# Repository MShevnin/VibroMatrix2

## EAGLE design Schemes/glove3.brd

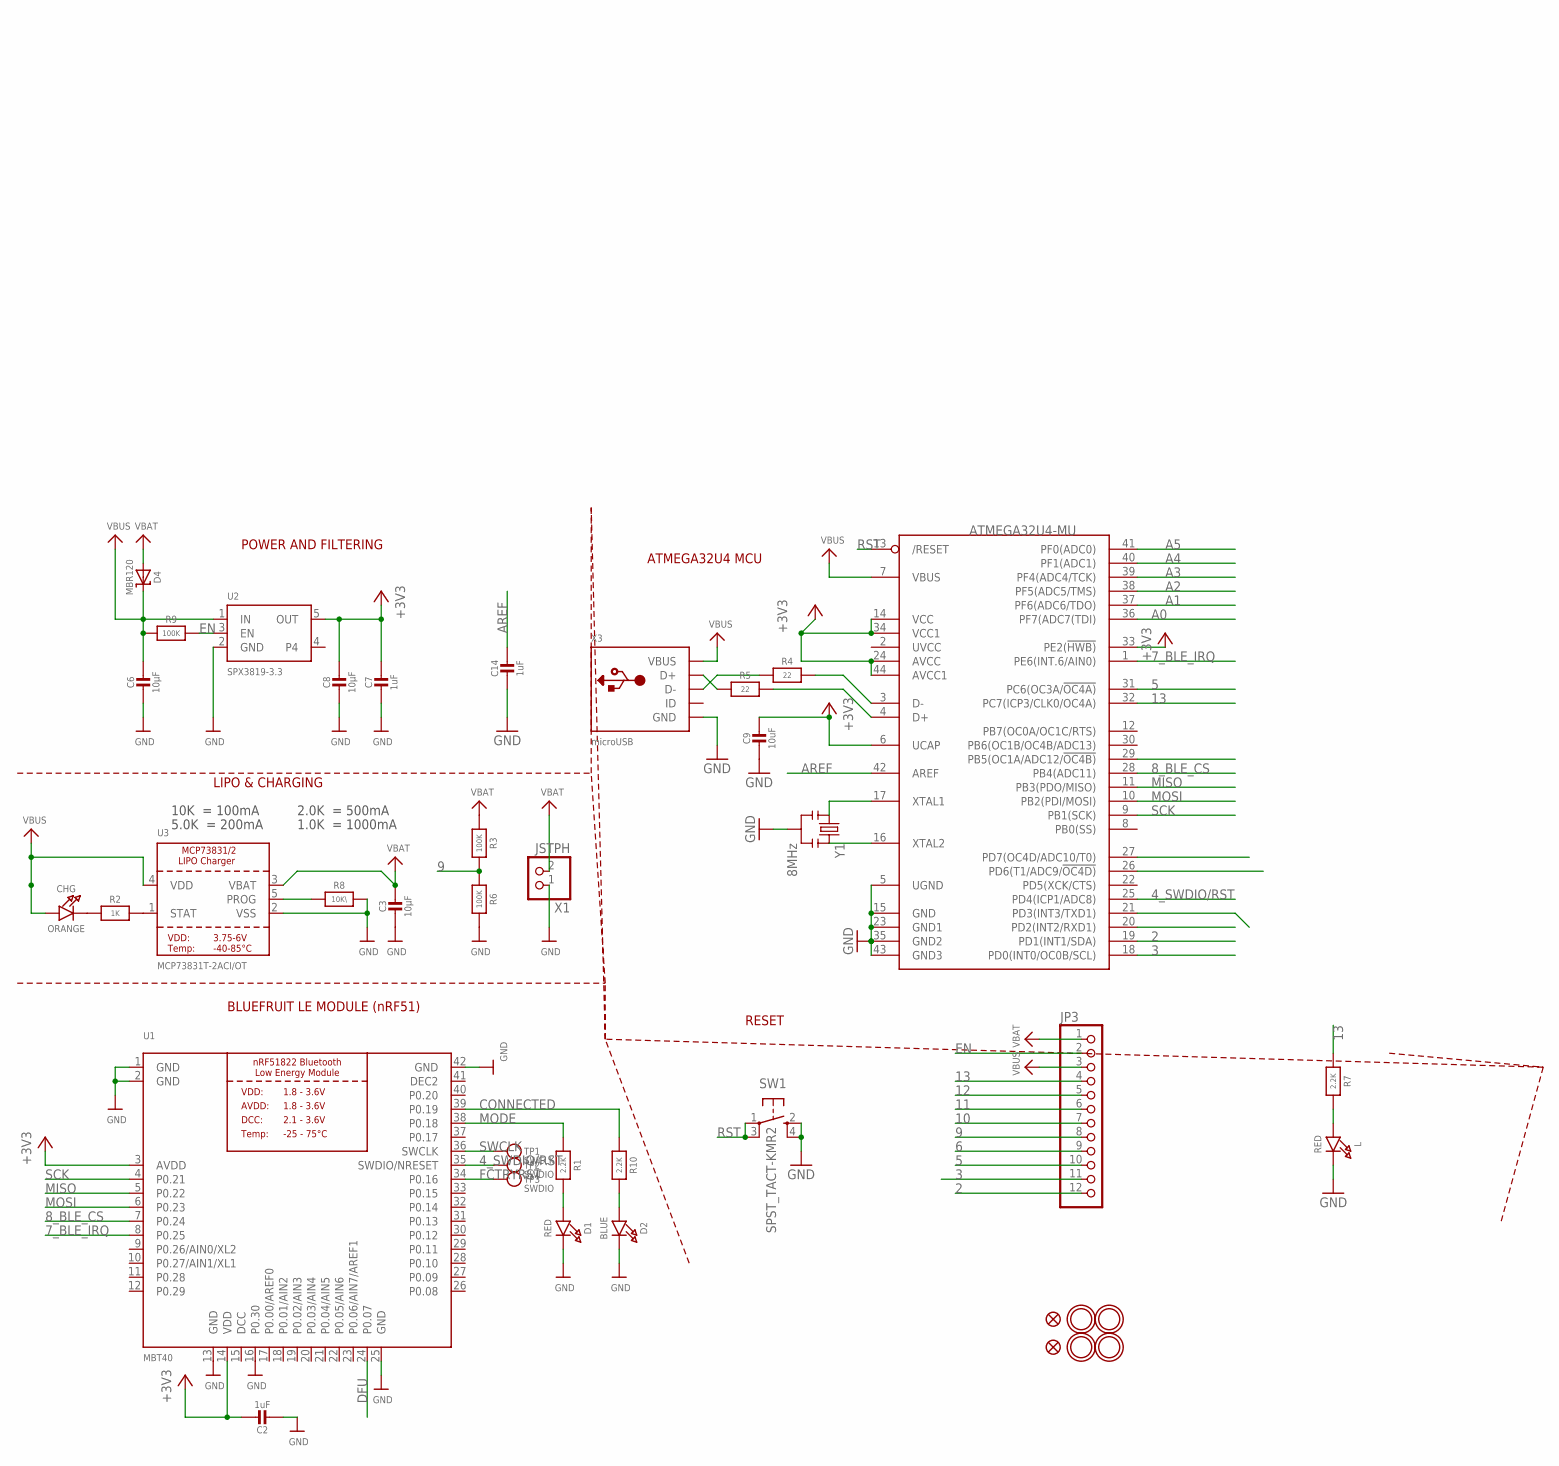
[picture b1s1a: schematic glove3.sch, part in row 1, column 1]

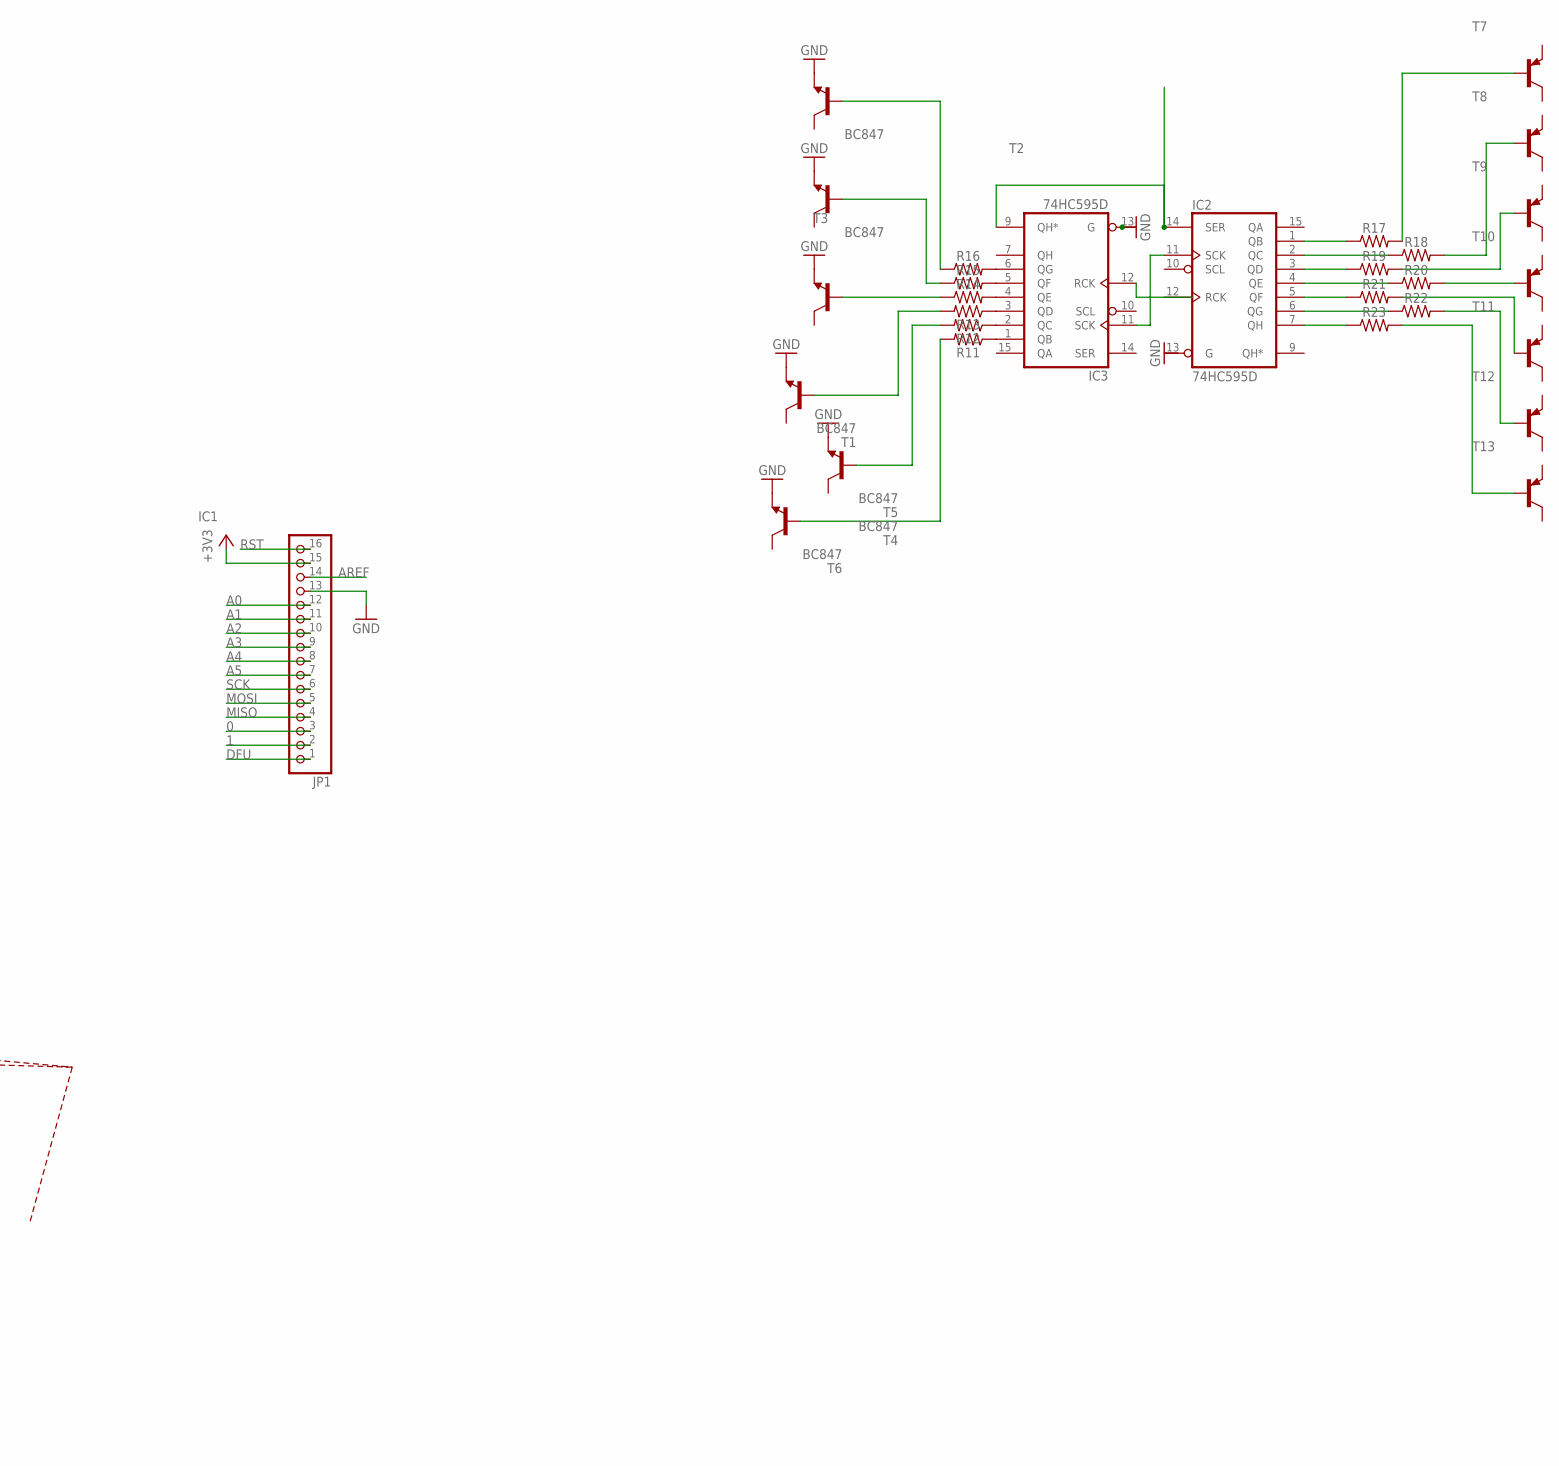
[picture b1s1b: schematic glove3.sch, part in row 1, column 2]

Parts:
C2, C7, C14: 1uF; 0603-NO
C3, C6, C8: 10µF; 0805-NO
C9: 10uF; _0805MP
CHG: ORANGE; CHIPLED_0805_NOOUTLINE
D1: RED; CHIPLED_0805_NOOUTLINE
D2: BLUE; CHIPLED_0805_NOOUTLINE
D4: MBR120; SOD-123
IC1: ATMEGA32U4-MU; TQFN44_7MM
IC2, IC3: 74HC595D; SO16
JP1: HEADER-1X16ROUND; 1X16_ROUND
JP3: HEADER-1X12; 1X12_ROUND
L: RED; CHIPLED_0805_NOOUTLINE
R1, R7, R10: 2.2K; 0603-NO
R2: 1K; 0603-NO
R3, R6, R9: 100K; 0603-NO
R4, R5: 22; 0603-NO
R8: 10K\; 0603-NO
R11, R12, R13, R14, R15, R16, R17, R18, R19, R20, R21, R22, R23: 1206
SW1: SPST_TACT-KMR2; KMR2
T1, T2, T3, T4, T5, T6: BC847; SOT23
T7, T8, T9, T10, T11, T12, T13: BC857C-PNP-SOT23-BEC; SOT23-BEC
TP1: SWCLK; PAD-1.5X2.0
TP2, TP3: SWDIO; PAD-1.5X2.0
U1: MBT40; BLE_MODULE_RAYTAC_MDBT40
U2: SPX3819-3.3; SOT23-5
U3: MCP73831T-2ACI/OT; SOT23-5
U$6, U$24, U$31, U$32: MOUNTINGHOLE2.5; MOUNTINGHOLE_2.5_PLATED
U$34, U$35: FIDUCIAL""; FIDUCIAL_1MM
X1: JSTPH; JSTPH2
X3: microUSB; 4UCONN_20329_V2
Y1: 8MHz; RESONATOR-SMD

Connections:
0: JP1.3
1: JP1.2
2: IC1.19 (PD1(INT1/SDA)), JP3.12
3: IC1.18 (PD0(INT0/OC0B/SCL)), JP3.11
4_SWDIO/RST: IC1.25 (PD4(ICP1/ADC8)), TP2.P$1, U1.35 (SWDIO/NRESET)
5: IC1.31 (PC6(OC3A/!OC4A)), JP3.10
6: JP3.9
7_BLE_IRQ: IC1.1 (PE6(INT.6/AIN0)), U1.8 (P0.25)
8_BLE_CS: IC1.28 (PB4(ADC11)), U1.7 (P0.24)
9: JP3.8, R3.2, R6.1
10: JP3.7
11: JP3.6
12: JP3.5
13: IC1.32 (PC7(ICP3/CLK0/OC4A)), JP3.4, R7.1
+3V3: C2.1, C7.1, C8.1, C9.1, IC1.6 (UCAP), IC1.14 (VCC), IC1.24 (AVCC), IC1.33 (PE2(!HWB)), IC1.34 (VCC1), IC1.44 (AVCC1), JP1.15, U1.3 (AVDD), U1.14 (VDD), U2.5 (OUT)
A0: IC1.36 (PF7(ADC7(TDI)), JP1.12
A1: IC1.37 (PF6(ADC6/TDO)), JP1.11
A2: IC1.38 (PF5(ADC5/TMS)), JP1.10
A3: IC1.39 (PF4(ADC4/TCK)), JP1.9
A4: IC1.40 (PF1(ADC1)), JP1.8
A5: IC1.41 (PF0(ADC0)), JP1.7
AREF: C14.1, IC1.42 (AREF), JP1.14
CONNECTED: R10.1, U1.39 (P0.19)
D+: IC1.4 (D+), R5.2
D-: IC1.3 (D-), R4.2
DCC: U1.15 (DCC)
DEC2: U1.41 (DEC2)
DFU: JP1.1, U1.24 (P0.07)
EN: JP3.2, R9.2, U2.3 (EN)
FCTRYRST: TP3.P$1, U1.34 (P0.16)
GND: C2.2, C3.2, C6.2, C7.2, C8.2, C9.2, C14.2, D1.C, D2.C, IC1.5 (UGND), IC1.15 (GND), IC1.23 (GND1), IC1.35 (GND2), IC1.43 (GND3), IC2.8 (GND), IC3.8 (GND), JP1.13, L.C, R6.2, R8.2, SW1.2 (S), SW1.4 (S1), T1.2 (E), T2.2 (E), T3.2 (E), T4.2 (E), T5.2 (E), T6.2 (E), U1.1 (GND), U1.2 (GND), U1.13 (GND), U1.16 (P0.30), U1.25 (GND), U1.42 (GND), U2.2 (GND), U3.2 (VSS), X1.1, X3.BASE@1 (GND), X3.BASE@2 (GND), X3.GND, X3.SPRT@1 (GND), X3.SPRT@2 (GND), X3.SPRT@3 (GND), X3.SPRT@4 (GND), Y1.2
MISO: IC1.11 (PB3(PDO/MISO)), JP1.4, U1.5 (P0.22)
MODE: R1.1, U1.38 (P0.18)
MOSI: IC1.10 (PB2(PDI/MOSI)), JP1.5, U1.6 (P0.23)
unnamed: CHG.C, R2.1
unnamed: L.A, R7.2
unnamed: R2.2, U3.1 (STAT)
unnamed: R8.1, U3.5 (PROG)
unnamed: D1.A, R1.2
unnamed: D2.A, R10.2
unnamed: IC3.4 (QE), R14.2
unnamed: IC3.6 (QG), R16.2
unnamed: IC3.5 (QF), R15.2
unnamed: IC3.3 (QD), R13.1
unnamed: IC1.16 (XTAL2), Y1.3
unnamed: IC1.17 (XTAL1), Y1.1
unnamed: IC3.2 (QC), R12.1
unnamed: IC3.1 (QB), R11.1
unnamed: R5.1, X3.D+
unnamed: R4.1, X3.D-
unnamed: R16.1, T2.1 (B)
unnamed: IC2.1 (QB), R17.1
unnamed: IC2.2 (QC), R18.1
unnamed: IC2.3 (QD), R19.1
unnamed: IC2.4 (QE), R20.1
unnamed: IC2.5 (QF), R21.1
unnamed: IC2.6 (QG), R22.1
unnamed: IC2.7 (QH), R23.1
unnamed: R17.2, T7.B
unnamed: R18.2, T8.B
unnamed: R19.2, T9.B
unnamed: R20.2, T10.B
unnamed: R21.2, T11.B
unnamed: R22.2, T12.B
unnamed: R23.2, T13.B
unnamed: IC2.14 (SER), IC3.9 (QH*)
unnamed: IC2.11 (SCK), IC3.11 (SCK)
unnamed: IC2.12 (RCK), IC3.12 (RCK)
unnamed: R15.1, T3.1 (B)
unnamed: R14.1, T4.1 (B)
unnamed: R13.2, T1.1 (B)
unnamed: R12.2, T5.1 (B)
unnamed: R11.2, T6.1 (B)
RST: IC1.13 (/RESET), JP1.16, SW1.1, SW1.3 (P1)
SCK: IC1.9 (PB1(SCK)), JP1.6, U1.4 (P0.21)
SWCLK: TP1.P$1, U1.36 (SWCLK)
VBAT: C3.1, D4.A, JP3.1, R3.1, U3.3 (VBAT), X1.2
VBUS: C6.1, CHG.A, D4.C, IC1.7 (VBUS), JP3.3, R9.1, U2.1 (IN), U3.4 (VDD), X3.VBUS
VCC: IC2.16 (VCC), IC3.16 (VCC)

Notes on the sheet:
POWER AND FILTERING
BLUEFRUIT LE MODULE (nRF51)
RESET
ATMEGA32U4 MCU
10K = 100mA
5.0K = 200mA
2.0K = 500mA
1.0K = 1000mA
LIPO & CHARGING

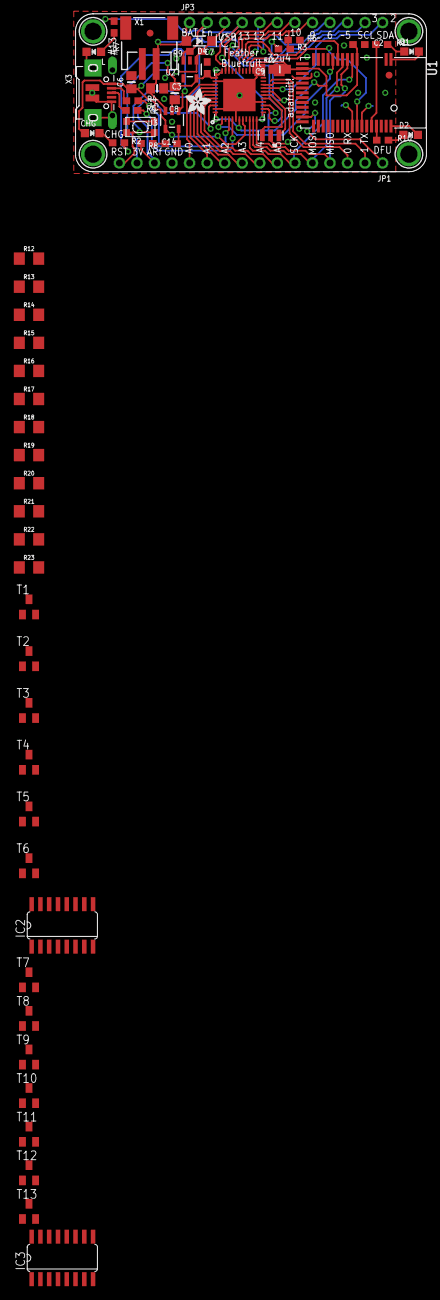
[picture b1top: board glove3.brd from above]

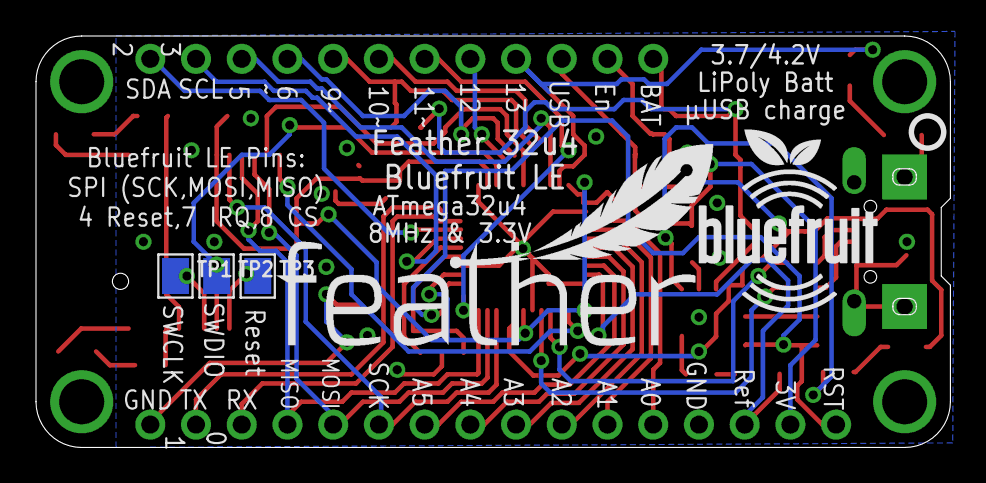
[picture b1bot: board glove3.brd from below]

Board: 2 copper layers, 50.8 x 22.9 mm, 73 parts (6 on the bottom side), 71 nets.

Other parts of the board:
U$7: ADAFRUIT_3.5MM
U$9: FEATHERLOGO
U$23: PCBFEAT-REV-040
U$26: BLUEFRUITLOGO_100MM

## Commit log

2018-11-07 Create test
2018-11-07 Start new schemes

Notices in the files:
parts and their libraries:
microbuilder: This work is placed in the public domain, and may be freely used for commercial and non-commercial work with the following conditions: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
SparkFun: Licensing: CC v3.0 Share-Alike You are welcome to use this library for commercial purposes.
